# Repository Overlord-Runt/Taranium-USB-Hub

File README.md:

# Taranium Hub

A USBa Hub designed by @Overlord-Runt // Taran The Idiot

## The Taranium USB Hub

This is a 4 port usb hub with 2 USBa ports and 2 USBc ports. It has a pair of A and C on each side of the board, allowing it to be reversable.

## PCB
### Schematic

The schematic uses a custom made symbol for the ic and is wired up to normal datasheet requirements. It boasts the ability to have 2 USBa and 2 USBc ports.

### PCB

Here you can see the pcb design files for this project.

The power lines use 0.5mm traces due to the extra current.

## CAD

This is the case for the USB Hub.\
It has just 2 parts and has a relatively simplistic design that still looks nice and detailed.\
It only uses 2 screws because In my experince that is more than enough and it also has no space to add any more.

It is recommended to print in PETG due to the amount of heat that the hub gives off.

## BOM

|Item|Qty|Price(USD)|Source|Notes|
|----|---|----------|------|-----|
|PCB|5|$5|JLCPCB||
|PCBa+shipping|5|$40|JLCPCB||
|USBa Male|1||https://jlcpcb.com/partdetail/Korean_HropartsElec-U_G_O4DD_W1/C98125||
|USBa Female|2||https://jlcpcb.com/partdetail/47411-903131A1011D10100/C46407||
|USBc Female|2||https://jlcpcb.com/partdetail/HOAUC-HYCW412_USBC16065B/C5342196||
|10µf Capacitor|7||https://jlcpcb.com/partdetail/20411-CL10A106KP8NNNC/C19702||
|USB Hub Chip|1||https://lcsc.com/product-detail/USB-ICs_CoreChips-SL2-1A_C192893.html||
|3d printed case|1||3d printer||
|M3W5L6 Heatsets|7|1.7|https://www.aliexpress.com/item/1005003582355741.html?spm=a2g0o.order_list.order_list_main.50.21221802eFqViq||
|M3 6mm screws|3|1.52|https://www.aliexpress.com/item/32810852732.html?spm=a2g0o.order_list.order_list_main.28.21221802eFqViq||
|M3 12mm screws|4|2.05|https://www.aliexpress.com/item/32810852732.html?spm=a2g0o.order_list.order_list_main.28.21221802eFqViq||
|Total||$50|||

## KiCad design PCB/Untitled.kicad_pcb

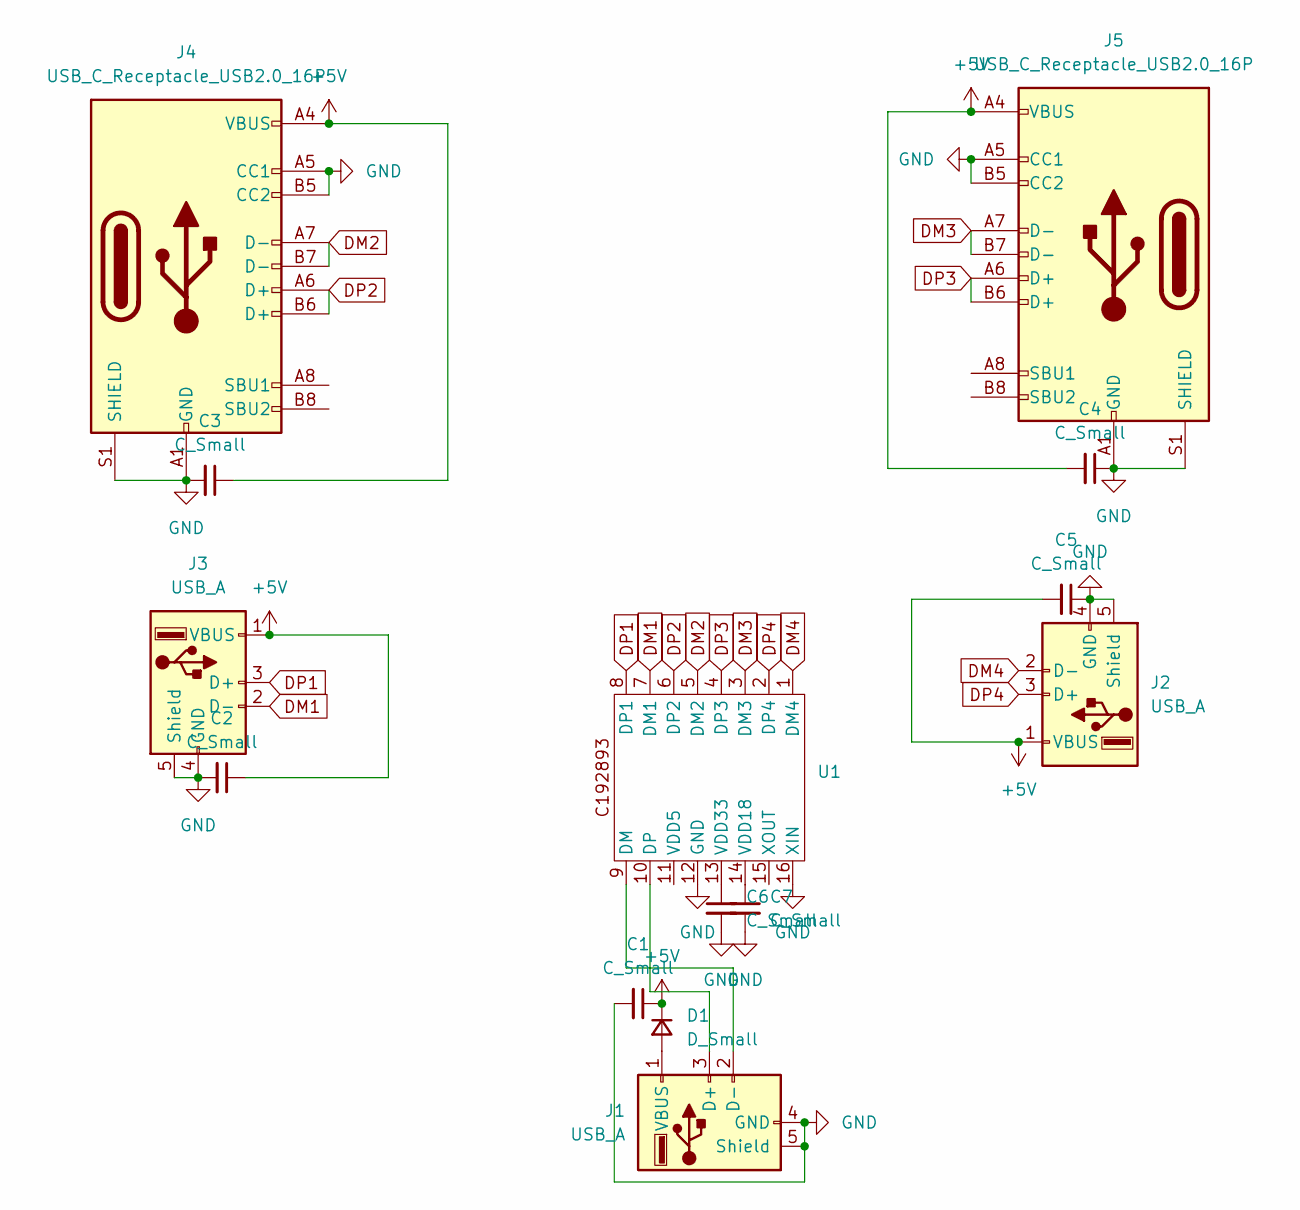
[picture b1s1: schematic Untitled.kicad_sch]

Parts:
C1, C2, C3, C4, C5, C6, C7: C_Small; C_0201_0603Metric
D1: D_Small; D_SOD-323
J1: USB_A; USB_A_Molex_48037-2200_Horizontal
J2, J3: USB_A; USB_A_Connfly_DS1095
J4, J5: USB_C_Receptacle_USB2.0_16P; USB_C_Receptacle_HCTL_HC-TYPE-C-16P-01A
U1: SO-16_3.9x9.9mm_P1.27mm

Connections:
+5V: C1.1, C2.1, C3.1, C4.2, C5.2, D1.1 (K), J2.1 (VBUS), J3.1 (VBUS), J4.A4 (VBUS), J4.A9 (VBUS), J4.B4 (VBUS), J4.B9 (VBUS), J5.A4 (VBUS), J5.A9 (VBUS), J5.B4 (VBUS), J5.B9 (VBUS)
DM1: J3.2 (D-), U1.7 (DM1)
DM2: J4.A7 (D-), J4.B7 (D-), U1.5 (DM2)
DM3: J5.A7 (D-), J5.B7 (D-), U1.3 (DM3)
DM4: J2.2 (D-), U1.1 (DM4)
DP1: J3.3 (D+), U1.8 (DP1)
DP2: J4.A6 (D+), J4.B6 (D+), U1.6 (DP2)
DP3: J5.A6 (D+), J5.B6 (D+), U1.4 (DP3)
DP4: J2.3 (D+), U1.2 (DP4)
GND: C1.2, C2.2, C3.2, C4.1, C5.1, C6.2, C7.2, J1.4 (GND), J1.5 (Shield), J2.4 (GND), J2.5 (Shield), J3.4 (GND), J3.5 (Shield), J4.A1 (GND), J4.A5 (CC1), J4.A12 (GND), J4.B1 (GND), J4.B5 (CC2), J4.B12 (GND), J4.S1 (SHIELD), J5.A1 (GND), J5.A5 (CC1), J5.A12 (GND), J5.B1 (GND), J5.B5 (CC2), J5.B12 (GND), J5.S1 (SHIELD), U1.12 (GND), U1.16 (XIN)
unnamed: D1.2 (A), J1.1 (VBUS)
unnamed: J1.3 (D+), U1.10 (DP)
unnamed: J1.2 (D-), U1.9 (DM)
unnamed: C7.1, U1.14 (VDD18)
unnamed: C6.1, U1.13 (VDD33)

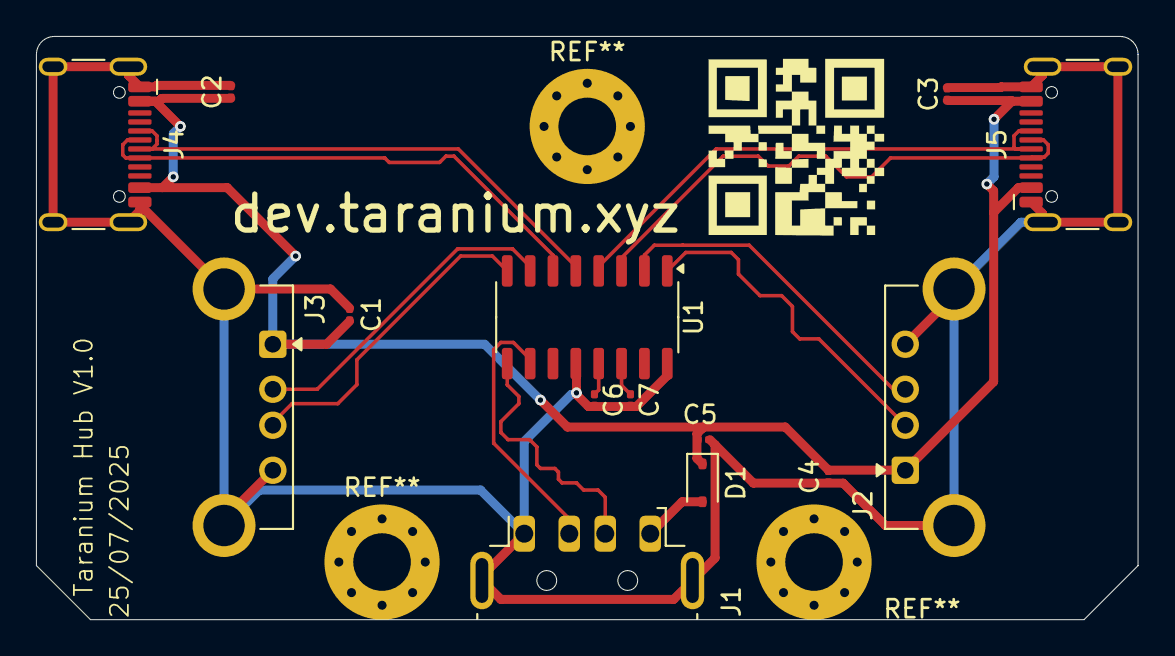
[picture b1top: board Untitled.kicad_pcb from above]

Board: 2 copper layers, 61.2 x 32.4 mm, 14 parts (0 on the bottom side), 15 nets.

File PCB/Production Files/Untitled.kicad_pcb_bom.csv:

Designator,Quantity,Value,Footprint,Package,MPN,DNP,Mount_Type,Description,Sim.Device,Sim.Pins
"C1, C2, C3, C4, C5, C6, C7",7,C_Small,C_0201_0603Metric,,,,smt,"Unpolarized capacitor, small symbol",,
D1,1,D_Small,D_SOD-323,,,,smt,"Diode, small symbol",D,1=K 2=A
J1,1,USB_A,USB_A_Molex_48037-2200_Horizontal,,,,smt,USB Type A connector,,
"J2, J3",2,USB_A,USB_A_Connfly_DS1095,,,,tht,USB Type A connector,,
"J4, J5",2,USB_C_Receptacle_USB2.0_16P,USB_C_Receptacle_HCTL_HC-TYPE-C-16P-01A,,,,smt,USB 2.0-only 16P Type-C Receptacle connector,,
U1,1,~,SO-16_3.9x9.9mm_P1.27mm,,,,smt,,,
